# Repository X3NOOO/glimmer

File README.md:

# Glimmer
Glimmer is an [WLED](https://github.com/wled/WLED) controller board. It supports all the most common LED strip voltages over 6.3mm jack and 5V over USB-C, audio reactivity, IR control, and driving two separate data channels at once.

<details>
<summary>Photos</summary>

[schematics.pdf](/images/schematics.pdf)

</details>

## OSHWLab Stars 2026
The project had to be remade in EasyEDA in order to be submitted to the OSHWLab Stars competition. I'm not the biggest fan of the program, but it is what it is.

If you like the project feel free to check out it's OSHWLab page and maybe even leave a like if you're generous like that.

Link to the project over there: https://oshwlab.com/x3no/project_caxlifbu

## Software
The controller is meant to run under WLED. Check their docs for info about configuration and flashing.
Website: https://kno.wled.ge/
Github: https://github.com/WLED/WLED

There is an USB autoflashing circuitry present on the board, but you can use the UART port as well. If you do want to do it you should desolder the 0-ohm R22 and R22 resistors - they bridge the USB-UART controller with the ESP32.

If you want to use WLED-MM a platformio compilation environment is available [here](https://gist.github.com/X3NOOO/2119d469b6a600acc29e1caa4ec98841).

### UART LEDs

If the TX/RX LEDs are not flashing when talking with the board via USB your CP2102N didn't come with TXT and RXT enabled by default. You can change that using the [Simplicity Studio 5](https://www.silabs.com/software-and-tools/simplicity-studio/simplicity-studio-version-5). Download it, connect the board, and change the GPIO settings from GPIO to TXT and RXT. Doing this is not neccesary for the board to work though.

## Usage
Flashed your board with WLED? Good, now it's the time to wire it up. The first thing to do is to place a properly rated fuse into the fuse holder. The [3557-2 fuseholder](https://www.keyelco.com/userAssets/file/K75p47.pdf) takes both standard and mini automotive fuses. You can calculate the fuse value using the WLED calculator. The big screw terminal is responsible for power delivery. When holding your controller with the USB port up and facing you:
- The first hole is VDC, it's the barrel jack input, except it's fused via the fuse you just put in.
- The second hole is VUSB, it's the same power your USB port supplies. There is an 2A polyfuse placed on it's line, so that's the limit on the power you can pull through it.
- The third hole is GND.

Then, there is the smaller screw terminal. It is used to communicate with your LEDs and houses the data lines. Both of them are levelshifted to 5V. The one on the left is mapped to your ESP32's GPIO23 and the right one is GPIO18.

Now you connect the inputs board. Place some doublesided tape on the back of it and secure it in the cutout on the shell. Wire the connector 1:1, you can check the pinout if you're not sure if you're doing it right.

## Case
The .stl files of the enclosure are available in the Releases tab.

## Pricing
Prices at JLCPCB.

### Controller
- $160: Price for 2 assembled and 3 bare PCBs. All in black.
- $100: Price for 2 assembled and 3 bare PCBs w/o the ESP32 which forces you to pick standard assembly.
- $30: Price for 2+3 with most of the extended components excluded if you're willing to source and solder them yourself.

### Inputs board
Header is not soldered in any of the variants.
- $70: 2 assembled and 3 bare ones.
- $20: 2 assembled and 3 bare ones w/o the microphone as it forces standard assembly.

### Shell
- Up to $10: 1 bottom + 1 top. 

### Additional
- 4x >33mm M2 screws.
- 4x M2 threaded M2 insert nuts. Length=2mm, OD=4mm.
- A bit of double sided tape if your Inputs Board doesn't hold in place.

## Get it
All the files necessary to get the board made at JLCPCB are available in the Releases tab. They include all the components, so you can expect a to see a high price if you use them as they are. You can tweak the assembly components after uploading the BOM to the website to lower the price.

## IMPORTANT
I am not an engineer - the PCB works, but I cannot guarantee it will not burn your house down. I do not take any responsibility for y'all being silly.

## Sidenotes
- Thank you to the (unfortunately dead) [yawl controller](https://github.com/lizardsystems/yawl-controller) project - I stole your levelshifter.

- Thank you to the creators of the [OSHWLab Stars](https://oshwlab.com/activities/stars2026) competition for making it possible to get this board manufactured in a reasonable price.

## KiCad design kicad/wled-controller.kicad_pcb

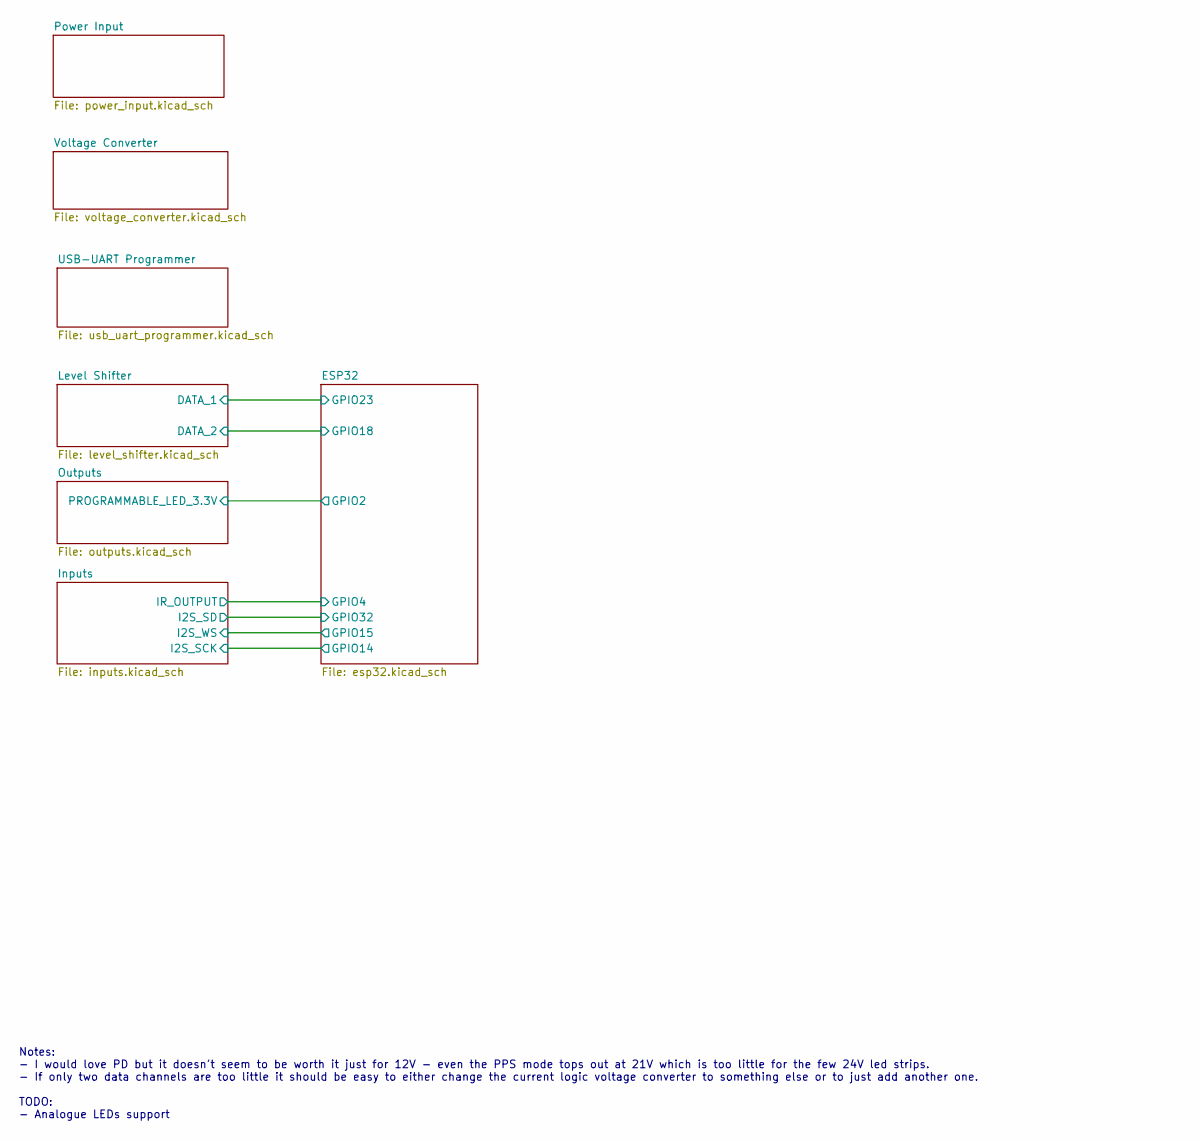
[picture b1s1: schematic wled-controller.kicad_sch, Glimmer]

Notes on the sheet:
Notes: - I would love PD but it doesn't seem to be worth it just for 12V - even the PPS mode tops out at 21V which is too little for the few 24V led strips. - If only two data channels are too little it should be easy to either change the current logic voltage converter to something else or to just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

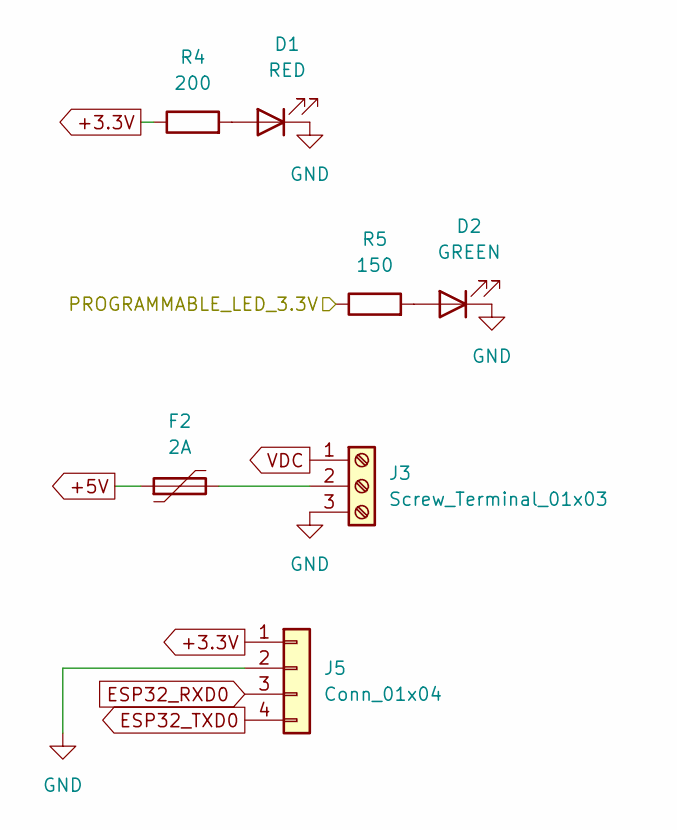
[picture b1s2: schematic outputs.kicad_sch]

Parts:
D1: RED; LED_0805_2012Metric_Pad1.15x1.40mm_HandSolder
D2: GREEN; LED_0805_2012Metric_Pad1.15x1.40mm_HandSolder
F2: 2A; 1206L075SLYR
J3: Screw_Terminal_01x03; TerminalBlock_TE_282834-3_1x03_P2.54mm_Horizontal
J5: Conn_01x04; NS-Tech_Grove_1x04_P2mm_Vertical
R4: 200; R_0805_2012Metric_Pad1.20x1.40mm_HandSolder
R5: 150; R_0805_2012Metric_Pad1.20x1.40mm_HandSolder

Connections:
+3.3V: J5.1, R4.1; also elsewhere on the board
+5V: F2.1; also elsewhere on the board
/ESP32/GPIO2: R5.1; also elsewhere on the board
ESP32_RXD0: J5.3; also elsewhere on the board
ESP32_TXD0: J5.4; also elsewhere on the board
GND: D1.1 (K), D2.1 (K), J3.3, J5.2; also elsewhere on the board
unnamed: D1.2 (A), R4.2
unnamed: D2.2 (A), R5.2
unnamed: F2.2, J3.2
VDC: J3.1; also elsewhere on the board

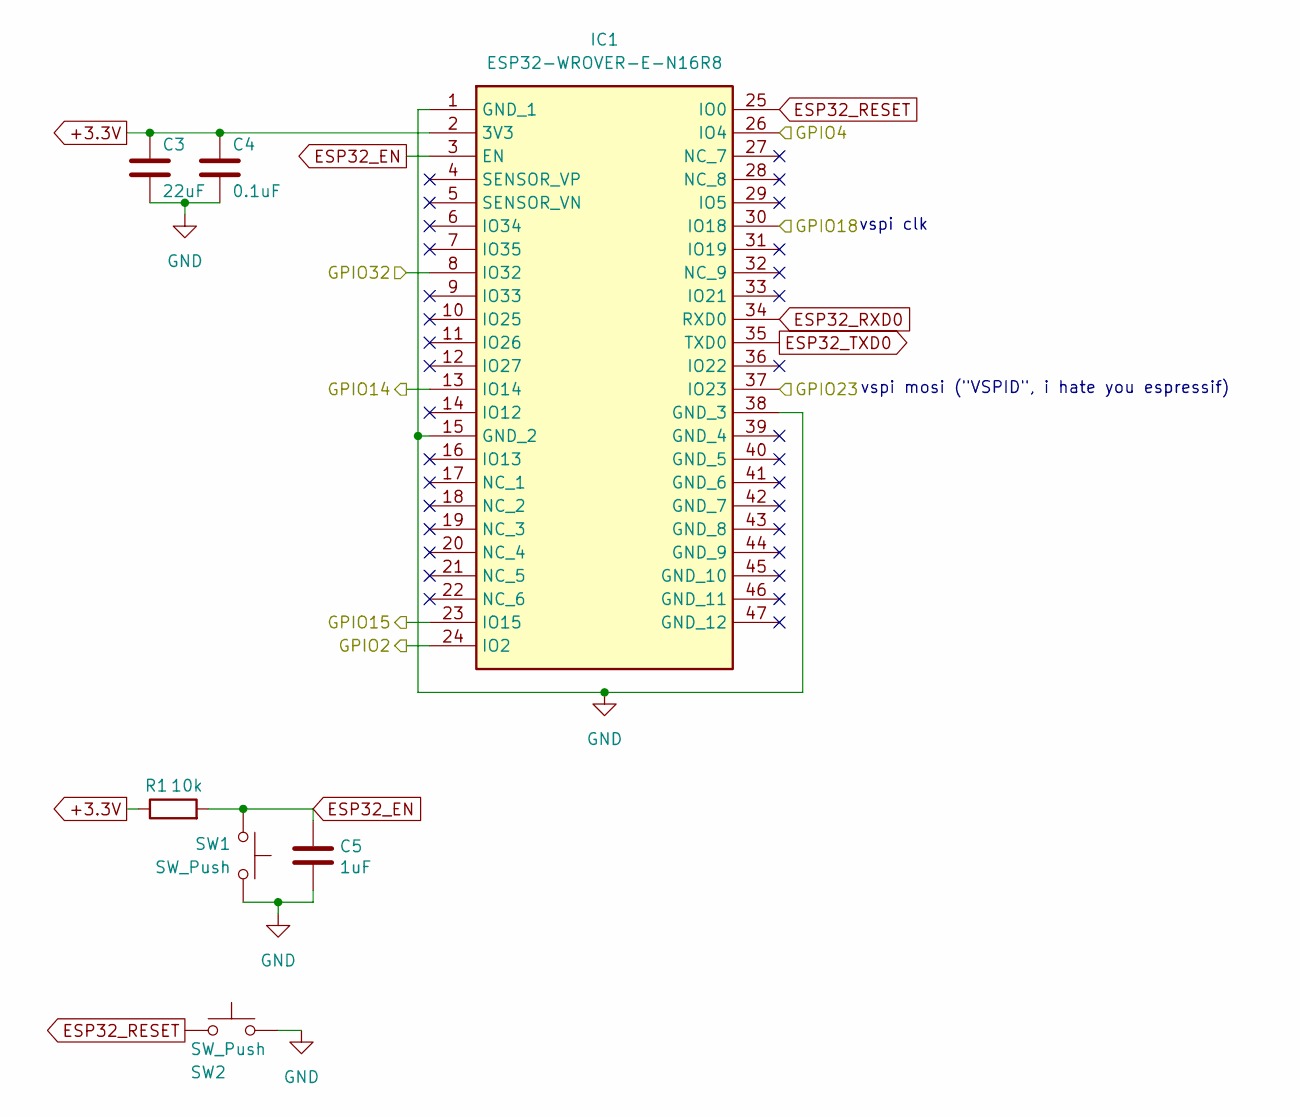
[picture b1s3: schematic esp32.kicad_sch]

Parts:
C3: 22uF; C_0805_2012Metric_Pad1.18x1.45mm_HandSolder
C4: 0.1uF; C_0805_2012Metric_Pad1.18x1.45mm_HandSolder
C5: 1uF; C_0805_2012Metric_Pad1.18x1.45mm_HandSolder
IC1: ESP32-WROVER-E-N16R8; ESP32WROVEREN16R8; Manufacturer_Part_Number ESP32-WROVER-E-N16R8; Mouser Part Number 356-ESP32WRVE22864PC
R1: 10k; R_0805_2012Metric_Pad1.20x1.40mm_HandSolder
SW1, SW2: SW_Push; SW_Push_1P1T_NO_CK_KMR2

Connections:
+3.3V: C3.1, C4.1, IC1.2 (3V3), R1.1; also elsewhere on the board
/ESP32/GPIO2: IC1.24 (IO2); also elsewhere on the board
/ESP32/GPIO4: IC1.26 (IO4); also elsewhere on the board
/ESP32/GPIO14: IC1.13 (IO14); also elsewhere on the board
/ESP32/GPIO15: IC1.23 (IO15); also elsewhere on the board
/ESP32/GPIO18: IC1.30 (IO18); also elsewhere on the board
/ESP32/GPIO23: IC1.37 (IO23); also elsewhere on the board
/ESP32/GPIO32: IC1.8 (IO32); also elsewhere on the board
ESP32_EN: C5.1, IC1.3 (EN), R1.2, SW1.1; also elsewhere on the board
ESP32_RESET: IC1.25 (IO0), SW2.1; also elsewhere on the board
ESP32_RXD0: IC1.34 (RXD0); also elsewhere on the board
ESP32_TXD0: IC1.35 (TXD0); also elsewhere on the board
GND: C3.2, C4.2, C5.2, IC1.1 (GND_1), IC1.15 (GND_2), IC1.38 (GND_3), SW1.2, SW2.2; also elsewhere on the board

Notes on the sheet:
vspi mosi ("VSPID", i hate you espressif)
vspi clk

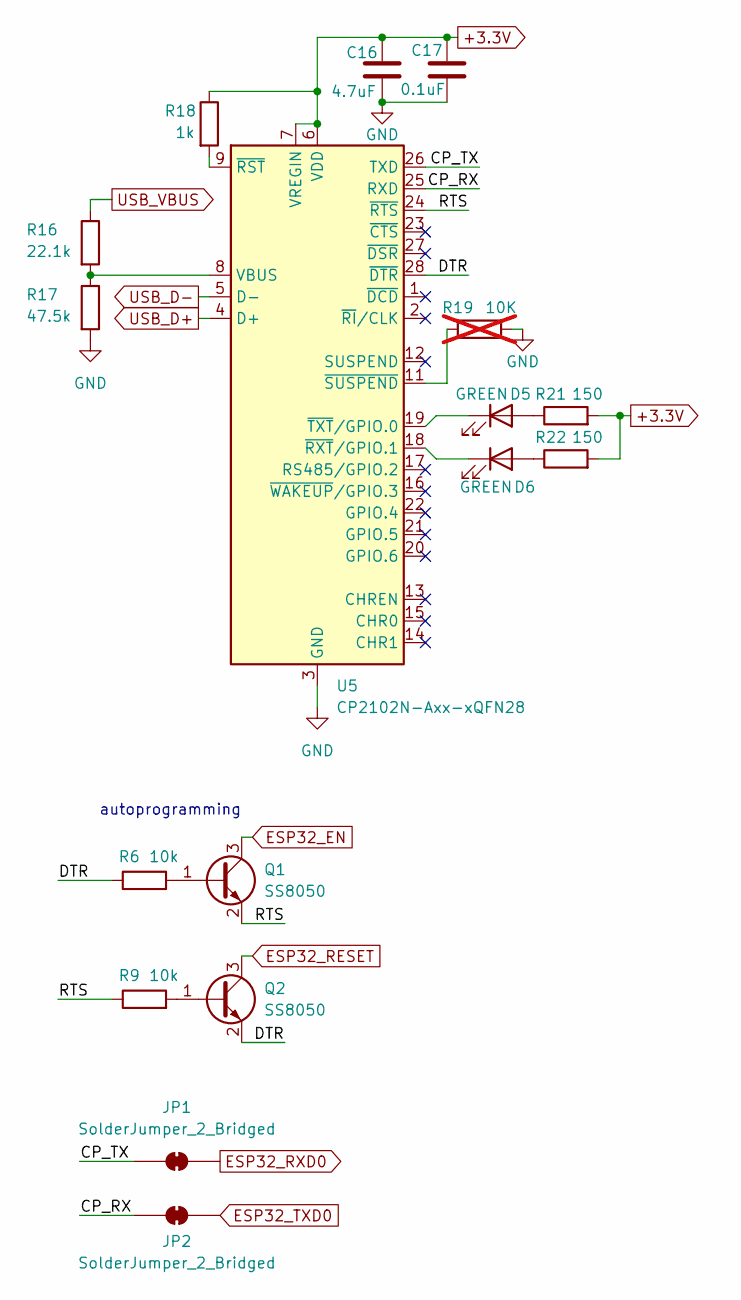
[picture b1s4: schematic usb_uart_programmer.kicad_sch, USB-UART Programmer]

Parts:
C16: 4.7uF; C_0805_2012Metric_Pad1.18x1.45mm_HandSolder
C17: 0.1uF; C_0805_2012Metric_Pad1.18x1.45mm_HandSolder
D5, D6: GREEN; LED_0805_2012Metric_Pad1.15x1.40mm_HandSolder
JP1, JP2: SolderJumper_2_Bridged; SolderJumper-2_P1.3mm_Open_TrianglePad1.0x1.5mm
Q1, Q2: SS8050; SOT-23
R6, R9: 10k; R_0805_2012Metric_Pad1.20x1.40mm_HandSolder
R16: 22.1k; R_0805_2012Metric_Pad1.20x1.40mm_HandSolder
R17: 47.5k; R_0805_2012Metric_Pad1.20x1.40mm_HandSolder
R18: 1k; R_0805_2012Metric_Pad1.20x1.40mm_HandSolder
R19: 10K; R_0805_2012Metric_Pad1.20x1.40mm_HandSolder; not fitted
R21, R22: 150; R_0805_2012Metric_Pad1.20x1.40mm_HandSolder
U5: CP2102N-Axx-xQFN28; QFN-28-1EP_5x5mm_P0.5mm_EP3.35x3.35mm

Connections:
+3.3V: C16.1, C17.1, R18.1, R21.2, R22.2, U5.6 (VDD), U5.7 (VREGIN); also elsewhere on the board
/USB-UART Programmer/CP_RX: JP2.1 (A), U5.25 (RXD)
/USB-UART Programmer/CP_TX: JP1.1 (A), U5.26 (TXD)
/USB-UART Programmer/DTR: Q2.2 (E), R6.1, U5.28 (~DTR)
/USB-UART Programmer/RTS: Q1.2 (E), R9.1, U5.24 (~RTS)
ESP32_EN: Q1.3 (C); also elsewhere on the board
ESP32_RESET: Q2.3 (C); also elsewhere on the board
ESP32_RXD0: JP1.2 (B); also elsewhere on the board
ESP32_TXD0: JP2.2 (B); also elsewhere on the board
GND: C16.2, C17.2, R17.2, R19.2, U5.3 (GND), U5.29 (GND); also elsewhere on the board
unnamed: D5.2 (A), R21.1
unnamed: D5.1 (K), U5.19 (~TXT/GPIO.0)
unnamed: D6.2 (A), R22.1
unnamed: D6.1 (K), U5.18 (~RXT/GPIO.1)
unnamed: Q1.1 (B), R6.2
unnamed: Q2.1 (B), R9.2
unnamed: R16.2, R17.1, U5.8 (VBUS)
unnamed: R18.2, U5.9 (~RST)
unnamed: R19.1, U5.11 (~SUSPEND)
USB_D+: U5.4 (D+); also elsewhere on the board
USB_D-: U5.5 (D-); also elsewhere on the board
USB_VBUS: R16.1; also elsewhere on the board

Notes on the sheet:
autoprogramming

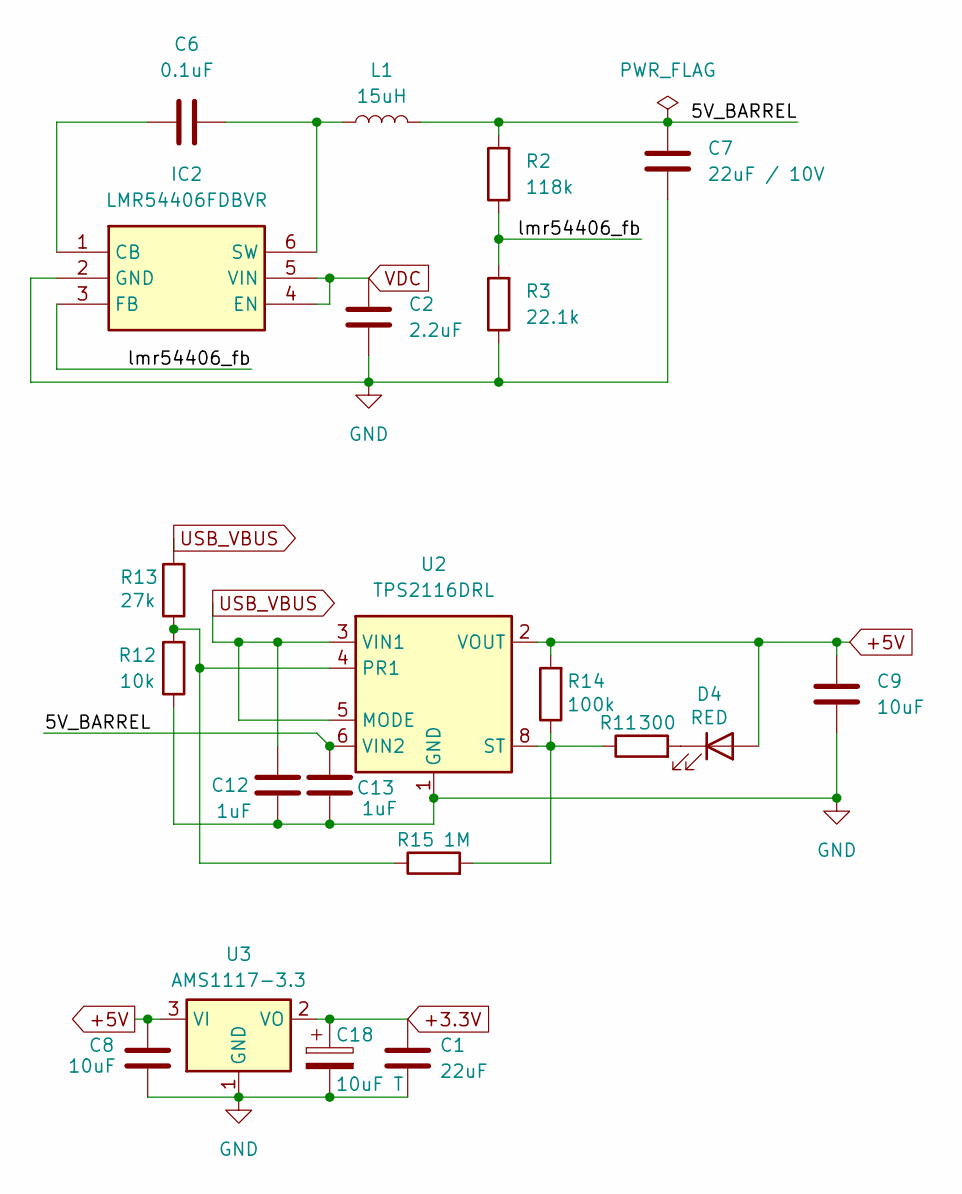
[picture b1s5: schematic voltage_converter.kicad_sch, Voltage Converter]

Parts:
C1: 22uF; C_0805_2012Metric_Pad1.18x1.45mm_HandSolder
C2: 2.2uF; C_0805_2012Metric_Pad1.18x1.45mm_HandSolder
C6: 0.1uF; C_0805_2012Metric_Pad1.18x1.45mm_HandSolder
C7: 22uF / 10V; C_0805_2012Metric_Pad1.18x1.45mm_HandSolder
C8, C9: 10uF; C_0805_2012Metric_Pad1.18x1.45mm_HandSolder
C12, C13: 1uF; C_0805_2012Metric_Pad1.18x1.45mm_HandSolder
C18: 10uF T; CP_EIA-2012-12_Kemet-R_HandSolder
D4: RED; LED_0805_2012Metric_Pad1.15x1.40mm_HandSolder
IC2: LMR54406FDBVR; SOT95P280X145-6N; Manufacturer_Part_Number LMR54406FDBVR; Mouser Part Number 595-LMR54406FDBVR
L1: 15uH; VLS3015
R2: 118k; R_0805_2012Metric_Pad1.20x1.40mm_HandSolder
R3: 22.1k; R_0805_2012Metric_Pad1.20x1.40mm_HandSolder
R11: 300; R_0805_2012Metric_Pad1.20x1.40mm_HandSolder
R12: 10k; R_0805_2012Metric_Pad1.20x1.40mm_HandSolder
R13: 27k; R_0805_2012Metric_Pad1.20x1.40mm_HandSolder
R14: 100k; R_0805_2012Metric_Pad1.20x1.40mm_HandSolder
R15: 1M; R_0805_2012Metric_Pad1.20x1.40mm_HandSolder
U2: TPS2116DRL; SOT-583-8
U3: AMS1117-3.3; SOT-223-3_TabPin2

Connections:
+3.3V: C1.1, C18.1, U3.2 (VO); also elsewhere on the board
+5V: C8.1, C9.1, D4.2 (A), R14.2, U2.2 (VOUT), U2.7 (VOUT), U3.3 (VI); also elsewhere on the board
/Voltage Converter/5V_BARREL: C7.1, C13.1, L1.2, R2.2, U2.6 (VIN2)
/Voltage Converter/lmr54406_fb: IC2.3 (FB), R2.1, R3.2
GND: C1.2, C2.2, C7.2, C8.2, C9.2, C12.2, C13.2, C18.2, IC2.2 (GND), R3.1, R12.1, U2.1 (GND), U3.1 (GND); also elsewhere on the board
unnamed: D4.1 (K), R11.2
unnamed: C6.1, IC2.1 (CB)
unnamed: C6.2, IC2.6 (SW), L1.1
unnamed: R12.2, R13.1, R15.1, U2.4 (PR1)
unnamed: R11.1, R14.1, R15.2, U2.8 (ST)
USB_VBUS: C12.1, R13.2, U2.3 (VIN1), U2.5 (MODE); also elsewhere on the board
VDC: C2.1, IC2.4 (EN), IC2.5 (VIN); also elsewhere on the board

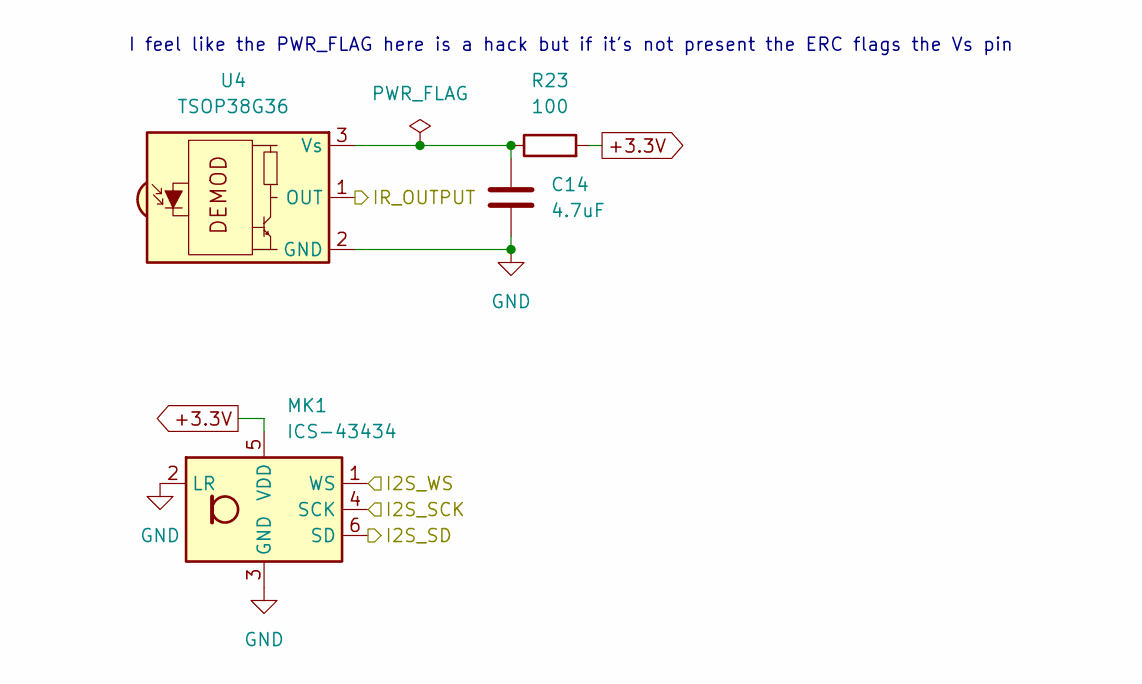
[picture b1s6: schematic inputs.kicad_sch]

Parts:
C14: 4.7uF; C_0805_2012Metric_Pad1.18x1.45mm_HandSolder
MK1: ICS-43434; PinHeader_2x03_P1.00mm_Vertical
R23: 100; R_0805_2012Metric_Pad1.20x1.40mm_HandSolder
U4: TSOP38G36; PinHeader_1x03_P1.00mm_Vertical

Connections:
+3.3V: MK1.5 (VDD), R23.2; also elsewhere on the board
/ESP32/GPIO4: U4.1 (OUT); also elsewhere on the board
/ESP32/GPIO14: MK1.4 (SCK); also elsewhere on the board
/ESP32/GPIO15: MK1.1 (WS); also elsewhere on the board
/ESP32/GPIO32: MK1.6 (SD); also elsewhere on the board
GND: C14.2, MK1.2 (LR), MK1.3 (GND), U4.2 (GND); also elsewhere on the board
unnamed: C14.1, R23.1, U4.3 (Vs)

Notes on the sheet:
I feel like the PWR_FLAG here is a hack but if it's not present the ERC flags the Vs pin

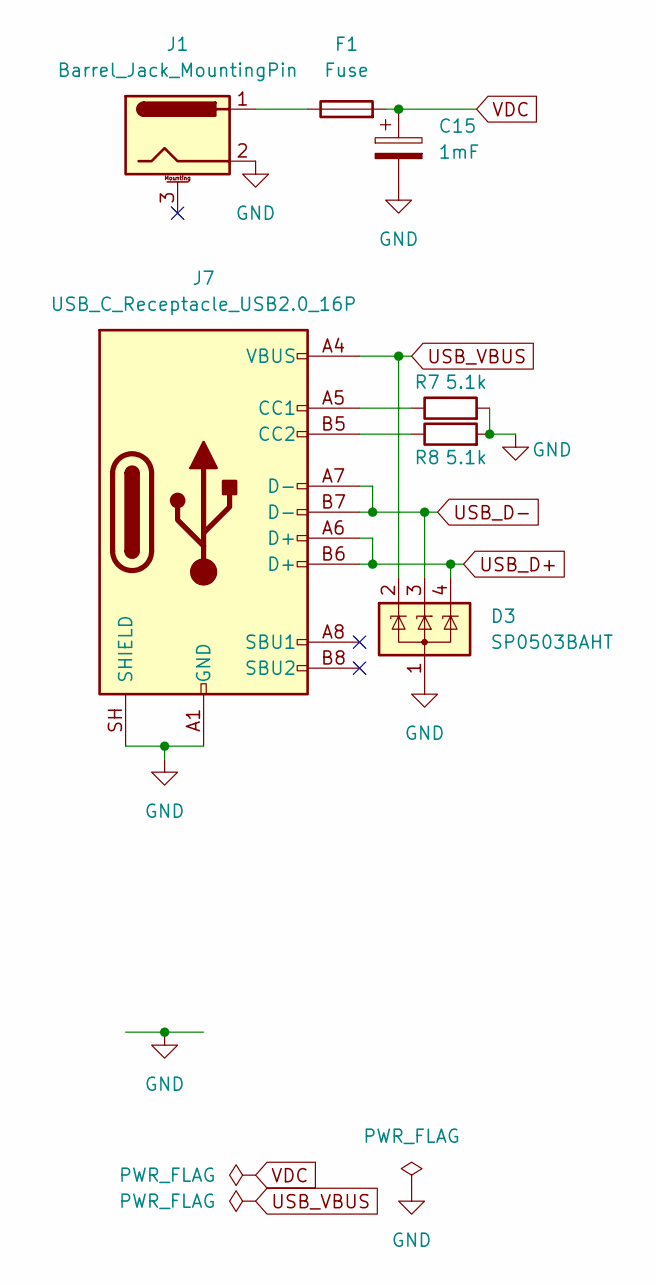
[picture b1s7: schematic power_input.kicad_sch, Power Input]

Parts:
C15: 1mF; CP_Radial_D16.0mm_P7.50mm
D3: SP0503BAHT; SOT-143
F1: Fuse; 3557-2
J1: Barrel_Jack_MountingPin; BarrelJack_GCT_DCJ200-10-A_Horizontal
J7: USB_C_Receptacle_USB2.0_16P; USB_C_Receptacle_GCT_USB4105-xx-A_16P_TopMnt_Horizontal
R7, R8: 5.1k; R_0805_2012Metric_Pad1.20x1.40mm_HandSolder

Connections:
GND: C15.2, D3.1 (A), J1.2, J7.A1 (GND), J7.A12 (GND), J7.B1 (GND), J7.B12 (GND), J7.SH (SHIELD), R7.2, R8.2; also elsewhere on the board
unnamed: F1.1, J1.1
unnamed: J7.A5 (CC1), R7.1
unnamed: J7.B5 (CC2), R8.1
USB_D+: D3.4 (K), J7.A6 (D+), J7.B6 (D+); also elsewhere on the board
USB_D-: D3.3 (K), J7.A7 (D-), J7.B7 (D-); also elsewhere on the board
USB_VBUS: D3.2 (K), J7.A4 (VBUS), J7.A9 (VBUS), J7.B4 (VBUS), J7.B9 (VBUS); also elsewhere on the board
VDC: C15.1, F1.2; also elsewhere on the board

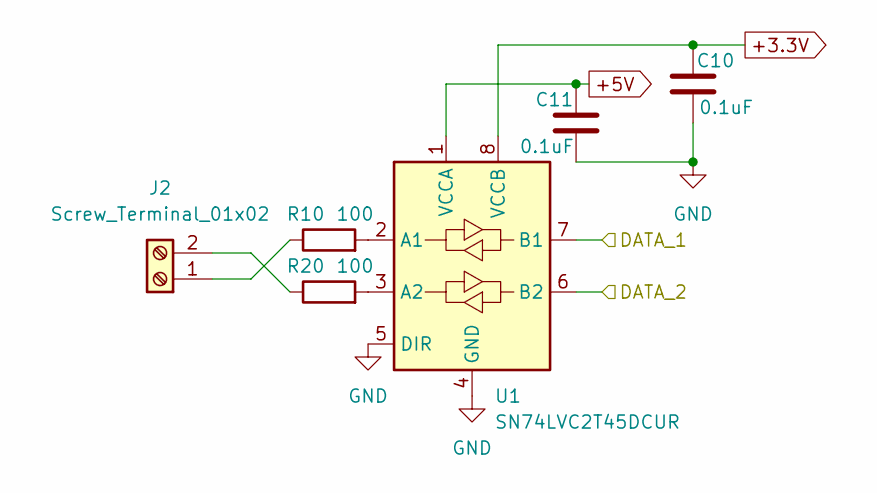
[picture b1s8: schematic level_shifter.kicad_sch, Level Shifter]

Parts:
C10, C11: 0.1uF; C_0805_2012Metric_Pad1.18x1.45mm_HandSolder
J2: Screw_Terminal_01x02; TerminalBlock_TE_282834-2_1x02_P2.54mm_Horizontal
R10, R20: 100; R_0805_2012Metric_Pad1.20x1.40mm_HandSolder
U1: SN74LVC2T45DCUR; VSSOP-8_2.3x2mm_P0.5mm

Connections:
+3.3V: C10.1, U1.8 (VCCB); also elsewhere on the board
+5V: C11.1, U1.1 (VCCA); also elsewhere on the board
/ESP32/GPIO18: U1.6 (B2); also elsewhere on the board
/ESP32/GPIO23: U1.7 (B1); also elsewhere on the board
GND: C10.2, C11.2, U1.4 (GND), U1.5 (DIR); also elsewhere on the board
unnamed: J2.1, R10.1
unnamed: J2.2, R20.1
unnamed: R10.2, U1.2 (A1)
unnamed: R20.2, U1.3 (A2)

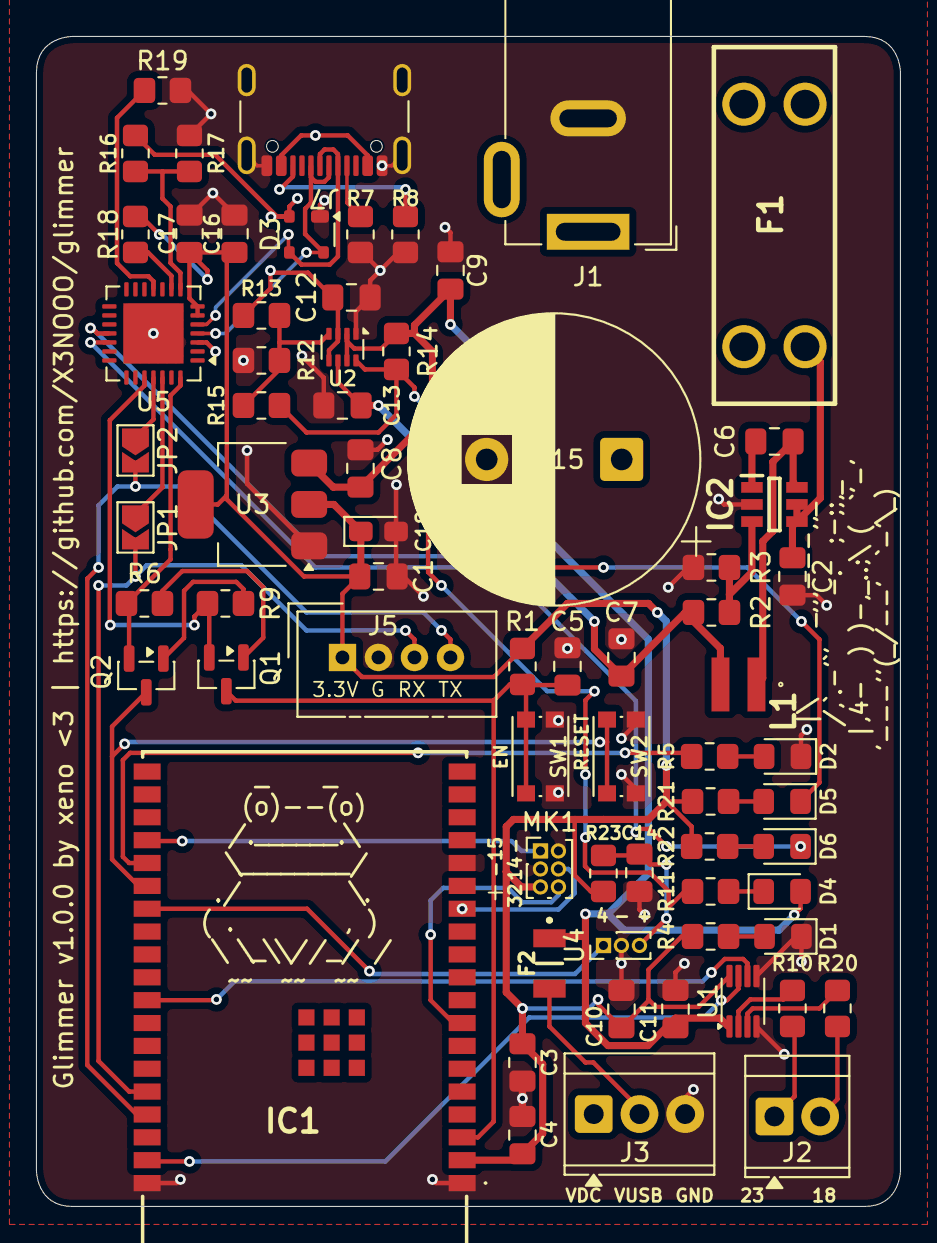
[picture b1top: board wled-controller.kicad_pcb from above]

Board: 4 copper layers, 48.0 x 65.0 mm, 69 parts (0 on the bottom side), 49 nets.

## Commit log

2026-05-05 typos
2026-05-05 added schematics
2026-06-13 v2.0.1
